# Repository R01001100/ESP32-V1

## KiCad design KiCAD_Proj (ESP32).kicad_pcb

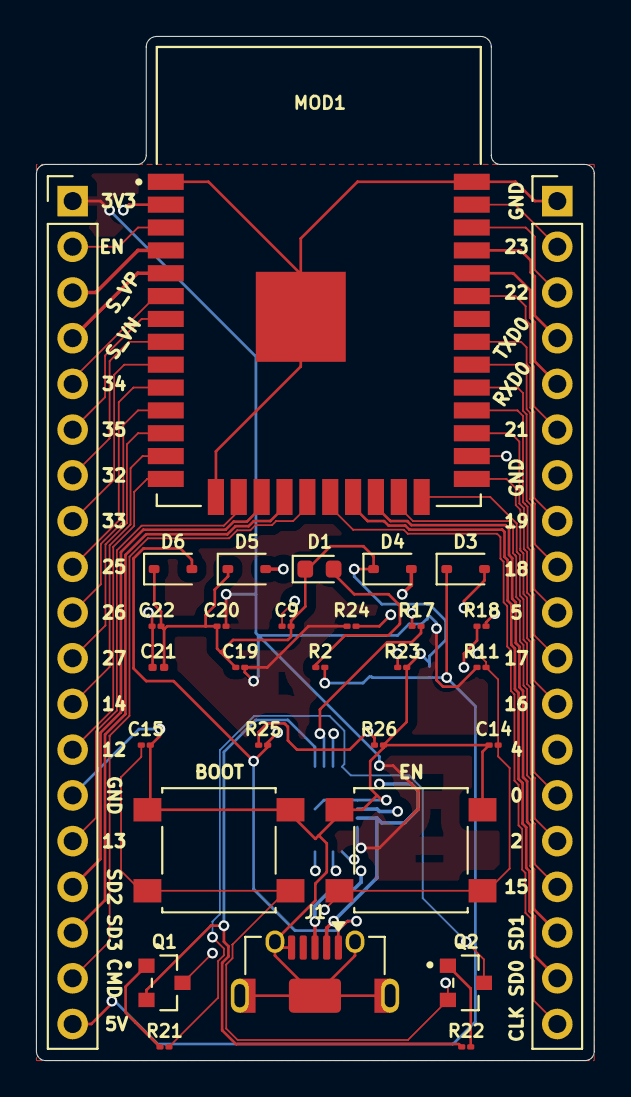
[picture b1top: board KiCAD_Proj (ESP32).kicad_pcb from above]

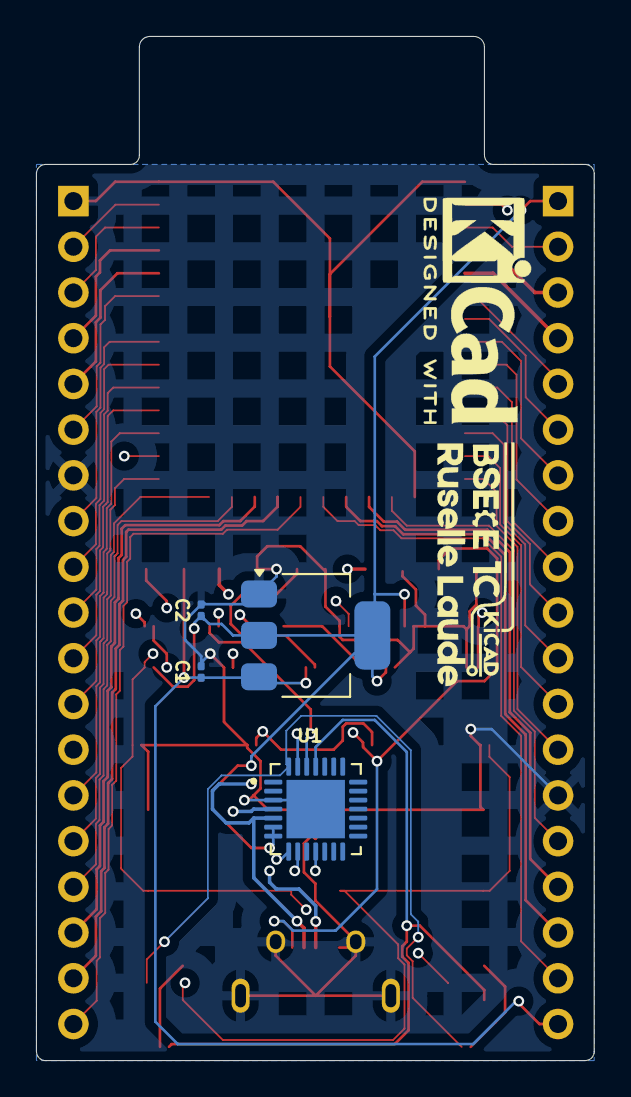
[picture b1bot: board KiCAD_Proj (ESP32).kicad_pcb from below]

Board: 4 copper layers, 31.0 x 56.9 mm, 34 parts (4 on the bottom side), 50 nets.

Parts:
C1, C2, C21: 22uF/10V(20%); C_0201_0603Metric
C9, C14, C15, C19, C22: 0.1uF/50V(10%); C_01005_0402Metric
C20: 4.7uF/6.3V(10%); C_01005_0402Metric
D1: LED; LED_0603_1608Metric
D3: D_Schottky; D_SOD-323
D4, D5, D6: D_TVS; D_SOD-323
J1: USB_B_Micro; USB_Micro-AB_Molex_47590-0001
J2, J3: Conn_01x19_Pin; PinHeader_1x19_P2.54mm_Vertical
MOD1: ESP32-WROOM-32; MODULE_ESP32-WROOM-32
Q1, Q2: MMSS8050-H-TP; TRANS_MMSS8050-H-TP
R2, R24: 2K(5%); R_01005_0402Metric
R11, R21, R22: 10K(5%); R_01005_0402Metric
R17, R18: 0R(5%); R_01005_0402Metric
R23: 10K(5%)(NC); R_01005_0402Metric
R25: 22.1K(5%); R_01005_0402Metric
R26: 47.5K(5%); R_01005_0402Metric
SW1, SW2: SW_Push; SW_SPST_B3S-1000
U1: CP2102N-A01-GQFN28; QFN50P500X500X80-29N
U2: AMS1117-3.3; SOT-223-3_TabPin2

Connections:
/CLK: J3.19, MOD1.20 (SCK/CLK)
/CMD: J2.18, MOD1.19 (SCS/CMD)
/DTR: Q2.3, R21.1, U1.28 (DTR)
/EN: C9.1, C14.2, J2.2, MOD1.3 (EN), Q1.3, R11.2, SW2.2
/EXT_5V: C1.1, D3.1 (K), J2.19, R2.1, U2.3 (VI)
/IO0: C15.2, J3.14, MOD1.25 (IO0), Q2.2, SW1.2
/IO2: J3.15, MOD1.24 (IO2)
/IO4: J3.13, MOD1.26 (IO4)
/IO5: J3.10, MOD1.29 (IO5)
/IO12: J2.13, MOD1.14 (IO12)
/IO13: J2.15, MOD1.16 (IO13)
/IO14: J2.12, MOD1.13 (IO14)
/IO15: J3.16, MOD1.23 (IO15)
/IO16: J3.12, MOD1.27 (IO16)
/IO17: J3.11, MOD1.28 (IO17)
/IO18: J3.9, MOD1.30 (IO18)
/IO19: J3.8, MOD1.31 (IO19)
/IO21: J3.6, MOD1.33 (IO21)
/IO22: J3.3, MOD1.36 (IO22)
/IO23: J3.2, MOD1.37 (IO23)
/IO25: J2.9, MOD1.10 (IO25)
/IO26: J2.10, MOD1.11 (IO26)
/IO27: J2.11, MOD1.12 (IO27)
/IO32: J2.7, MOD1.8 (IO32)
/IO33: J2.8, MOD1.9 (IO33)
/IO34: J2.5, MOD1.6 (IO34)
/IO35: J2.6, MOD1.7 (IO35)
/RTS: Q1.2, R22.1, U1.25 (RXD)
/RXD: R17.2, U1.26 (TXD)
/RXD0: J3.5, MOD1.34 (RXD0), R18.1
/SD0: J3.18, MOD1.21 (SDO/SD0)
/SD1: J3.17, MOD1.22 (SDI/SD1)
/SD2: J2.16, MOD1.17 (SHD/SD2)
/SD3: J2.17, MOD1.18 (SWP/SD3)
/SENSOR_VN: J2.4, MOD1.5 (SENSOR_VN)
/SENSOR_VP: J2.3, MOD1.4 (SENSOR_VP)
/TXD: R18.2, U1.27 (DSR)
/TXD0: J3.4, MOD1.35 (TXD0), R17.1
/USB_DN: D4.2 (A2), J1.2 (D-), U1.5 (D-)
/USB_DP: D5.2 (A2), J1.3 (D+), U1.4 (D+)
/VBUS: D3.2 (A), D6.2 (A2), J1.1 (VBUS), R25.2
/VDD33: C2.1, C19.1, C20.1, J2.1, R11.1, R24.1, U1.6 (VDD), U1.7 (VREGIN), U2.2 (VO)
GND: C1.2, C2.2, C9.2, C14.1, C15.1, C19.2, C20.2, C21.2, C22.2, D1.1 (K), D4.1 (A1), D5.1 (A1), D6.1 (A1), J1.5 (GND), J1.6 (Shield), J2.14, J3.1, J3.7, MOD1.1 (GND), MOD1.15 (GND), MOD1.38 (GND), MOD1.39 (GND), R23.2, R26.2, SW1.1, SW2.1, U1.3 (GND), U1.29 (GND), U2.1 (GND)
unnamed: D1.2 (A), R2.2
unnamed: Q1.1, R21.2
unnamed: Q2.1, R22.2
unnamed: R25.1, R26.1, U1.8 (VBUS)
unnamed: R24.2, U1.9 (~RST)
unnamed: R23.1, U1.11 (~SUSPENDB)
unnamed: C21.1, C22.1, MOD1.2 (3V3)

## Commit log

2025-10-20 Modified the gitignore
2025-10-25 Finished the schematic diagram and PCB board
2025-10-25 Added "READ ME" file
2025-10-25 Finished
